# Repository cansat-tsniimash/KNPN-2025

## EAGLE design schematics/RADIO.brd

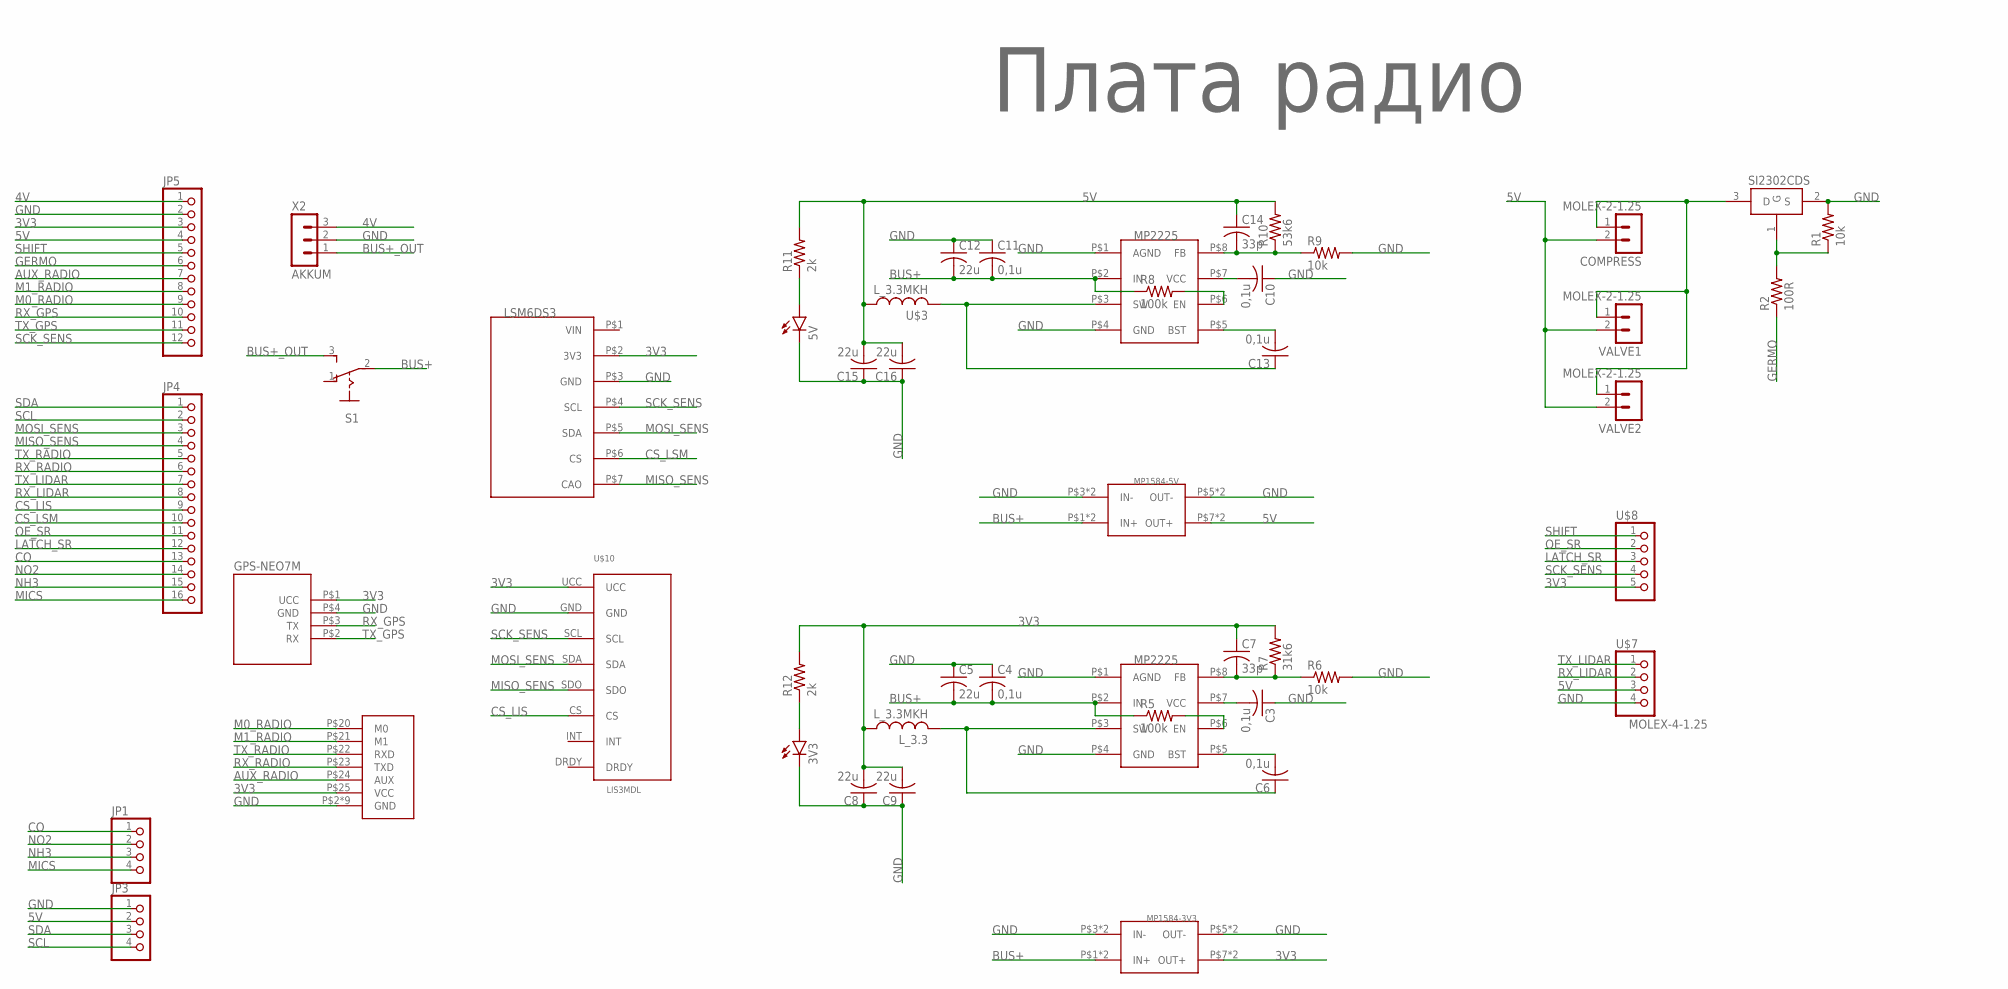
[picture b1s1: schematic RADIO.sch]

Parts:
3V3, 5V: LEDCHIP-LED0603; CHIP-LED0603
C3, C6, C10, C13: 0,1u; C0603
C4, C11: 0,1u; C1206
C5, C12: 22u; C0603
C7, C14: 33p; C0603
C8, C9, C15, C16: 22u; C1206
COMPRESS: MOLEX-2-1.25; 53047-02
GPS-NEO7M: GPS-NEO7M
JP1, JP3: PINHD-1X4; 1X04
JP4: PINHD-1X16; 1X16
JP5: PINHD-1X12; 1X12
LSM6DS3: LSM6DS3; LSM6DS3_WITHOUT
L_3.3: L_3.3MKH; L_SPM5020
MP1584-3V3: MP1584-B
MP1584-5V: MP1584; MP1584-B
R1, R6, R9: 10k; R0603
R2: 100R; R0603
R5, R8: 100k; R0603
R7: 31k6; R0603
R10: 53k6; R0603
R11, R12: 2k; R0603
RADIO: E220-400T22S
S1: UNICS-SWITCHSS_12D11; SS_12D11
SI2302CDS: SI2302CDS; SOT23-3
U$1: Плата радио; LOGO
U$2, U$5: MP2225; TSOT23-8
U$3: L_3.3MKH; L_SPM5020
U$7: MOLEX-4-1.25; 53047-04
U$8: MOLEX-5-1.25; 53047-05
U$10: LIS3MDL
VALVE1, VALVE2: MOLEX-2-1.25; 53047-02
X2: AKKUM; JST-3-2.5

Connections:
3V3: C7.1, C8.2, C9.2, GPS-NEO7M.P$1 (UCC), JP5.3, LSM6DS3.P$2 (3V3), L_3.3.P$1 (1), MP1584-3V3.P$7 (OUT+), MP1584-3V3.P$8 (OUT+), R7.2, R12.2, RADIO.P$25 (VCC), U$8.5, U$10.UCC
4V: JP5.1, X2.3
5V: C14.1, C15.2, C16.2, COMPRESS.2, JP3.2, JP5.4, MP1584-5V.P$7 (OUT+), MP1584-5V.P$8 (OUT+), R10.2, R11.2, U$3.P$1 (1), U$7.3, VALVE1.2, VALVE2.2
AUX_RADIO: JP5.7, RADIO.P$24 (AUX)
BUS+: C4.2, C5.2, C11.2, C12.2, MP1584-3V3.P$1 (IN+), MP1584-3V3.P$2 (IN+), MP1584-5V.P$1 (IN+), MP1584-5V.P$2 (IN+), R5.1, R8.1, S1.2, U$2.P$2 (IN), U$5.P$2 (IN)
BUS+_OUT: S1.3 (S), X2.1
CO: JP1.1, JP4.13
CS_LIS: JP4.9, U$10.CS
CS_LSM: JP4.10, LSM6DS3.P$6 (CS)
GERMO: JP5.6, R2.1
GND: 3V3.C, 5V.C, C3.1, C4.1, C5.1, C8.1, C9.1, C10.1, C11.1, C12.1, C15.1, C16.1, GPS-NEO7M.P$4 (GND), JP3.1, JP5.2, LSM6DS3.P$3 (GND), MP1584-3V3.P$3 (IN-), MP1584-3V3.P$4 (IN-), MP1584-3V3.P$5 (OUT-), MP1584-3V3.P$6 (OUT-), MP1584-5V.P$3 (IN-), MP1584-5V.P$4 (IN-), MP1584-5V.P$5 (OUT-), MP1584-5V.P$6 (OUT-), R1.2, R6.2, R9.2, RADIO.P$2 (GND), RADIO.P$8 (GND), RADIO.P$11 (GND), RADIO.P$13 (GND), RADIO.P$14 (GND), RADIO.P$15 (GND), RADIO.P$16 (GND), RADIO.P$19 (GND), RADIO.P$26 (GND), SI2302CDS.2 (S), U$2.P$1 (AGND), U$2.P$4 (GND), U$5.P$1 (AGND), U$5.P$4 (GND), U$7.4, U$10.GND, X2.2
LATCH_SR: JP4.12, U$8.3
M0_RADIO: JP5.9, RADIO.P$20 (M0)
M1_RADIO: JP5.8, RADIO.P$21 (M1)
MICS: JP1.4, JP4.16
MISO_SENS: JP4.4, LSM6DS3.P$7 (CAO), U$10.SDO
MOSI_SENS: JP4.3, LSM6DS3.P$5 (SDA), U$10.SDA
unnamed: R1.1, R2.2, SI2302CDS.1 (G)
unnamed: COMPRESS.1, SI2302CDS.3 (D), VALVE1.1, VALVE2.1
unnamed: C3.2, U$2.P$7 (VCC)
unnamed: R5.2, U$2.P$6 (EN)
unnamed: C6.2, U$2.P$5 (BST)
unnamed: C6.1, L_3.3.P$2 (2), U$2.P$3 (SW)
unnamed: C7.2, R6.1, R7.1, U$2.P$8 (FB)
unnamed: C10.2, U$5.P$7 (VCC)
unnamed: R8.2, U$5.P$6 (EN)
unnamed: C13.2, U$5.P$5 (BST)
unnamed: C13.1, U$3.P$2 (2), U$5.P$3 (SW)
unnamed: C14.2, R9.1, R10.1, U$5.P$8 (FB)
unnamed: 5V.A, R11.1
unnamed: 3V3.A, R12.1
NH3: JP1.3, JP4.15
NO2: JP1.2, JP4.14
OE_SR: JP4.11, U$8.2
RX_GPS: GPS-NEO7M.P$3 (TX), JP5.10
RX_LIDAR: JP4.8, U$7.2
RX_RADIO: JP4.6, RADIO.P$23 (TXD)
SCK_SENS: JP5.12, LSM6DS3.P$4 (SCL), U$8.4, U$10.SCL
SCL: JP3.4, JP4.2
SDA: JP3.3, JP4.1
SHIFT: JP5.5, U$8.1
TX_GPS: GPS-NEO7M.P$2 (RX), JP5.11
TX_LIDAR: JP4.7, U$7.1
TX_RADIO: JP4.5, RADIO.P$22 (RXD)

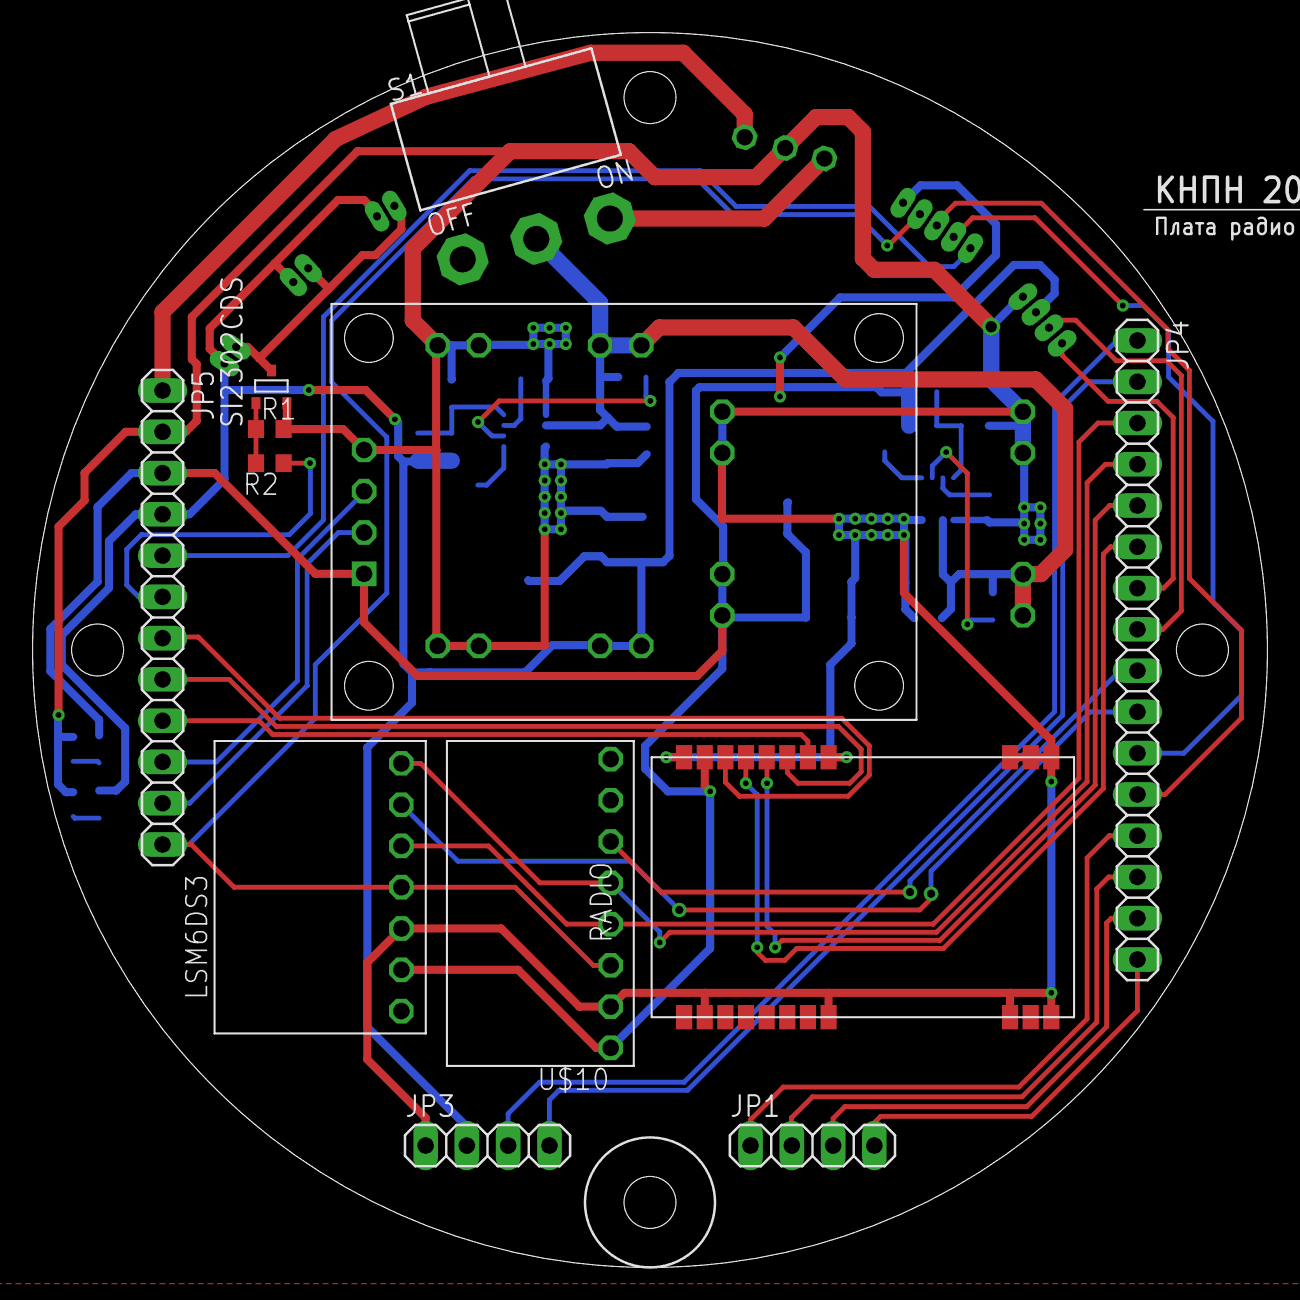
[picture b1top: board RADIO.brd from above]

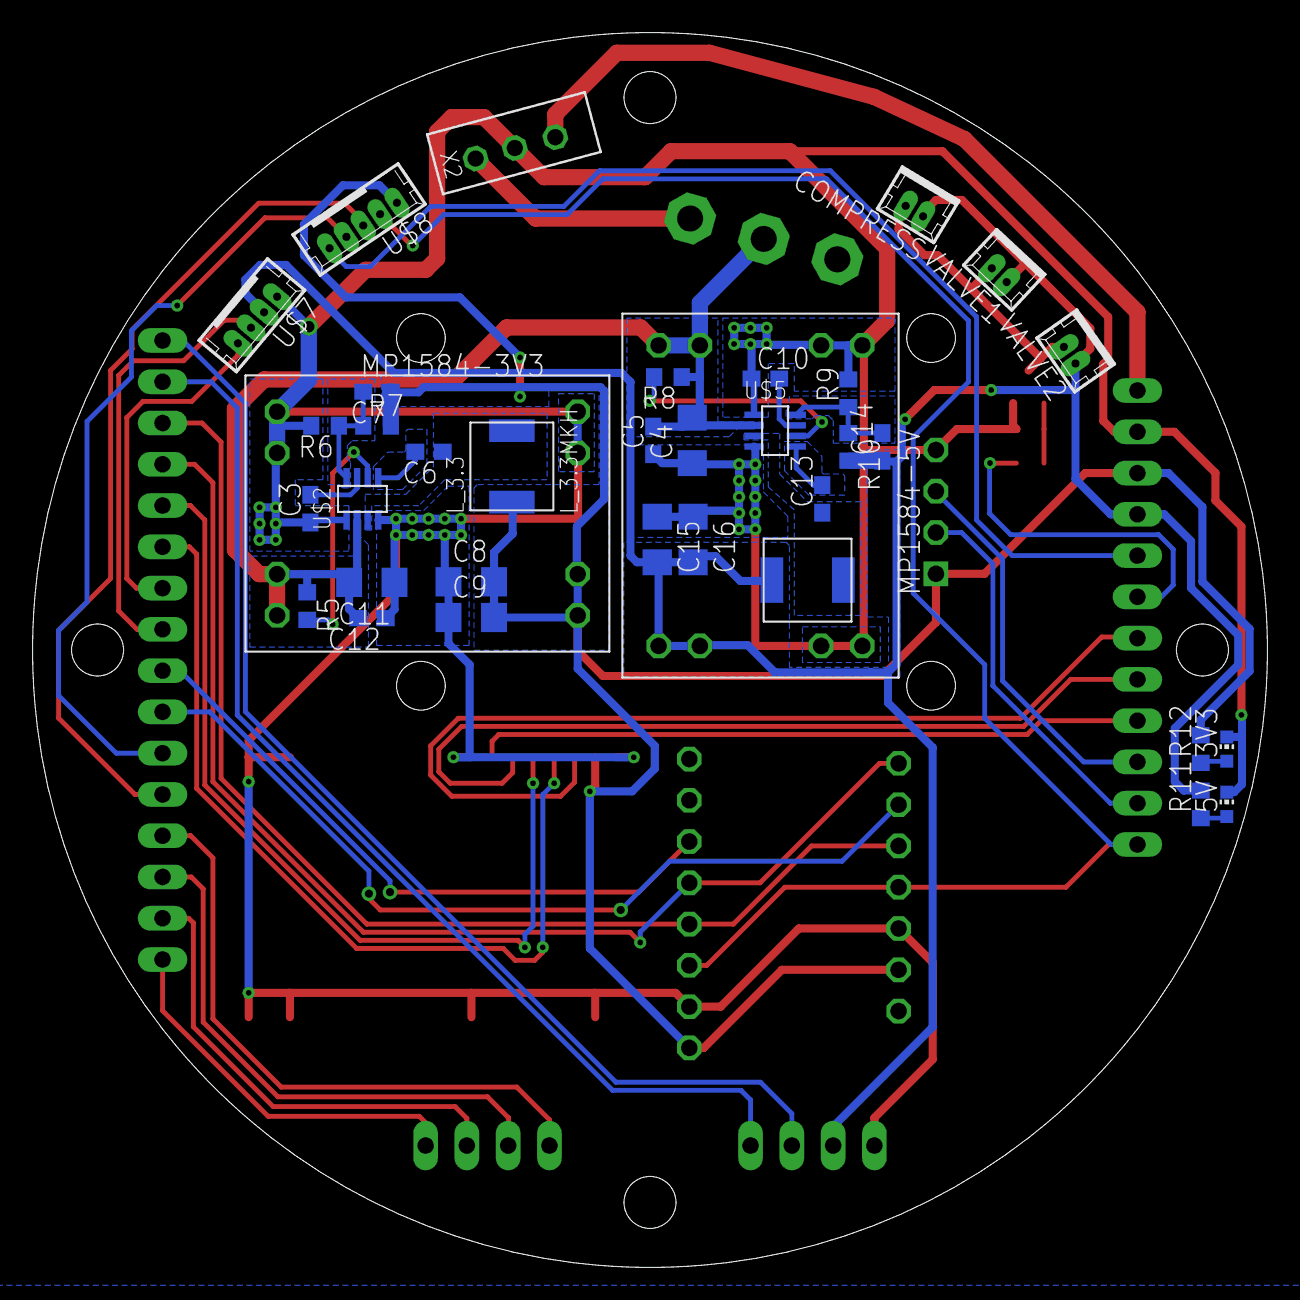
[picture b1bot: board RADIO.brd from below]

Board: 2 copper layers, 76.0 x 76.0 mm, 49 parts (36 on the bottom side), 44 nets.

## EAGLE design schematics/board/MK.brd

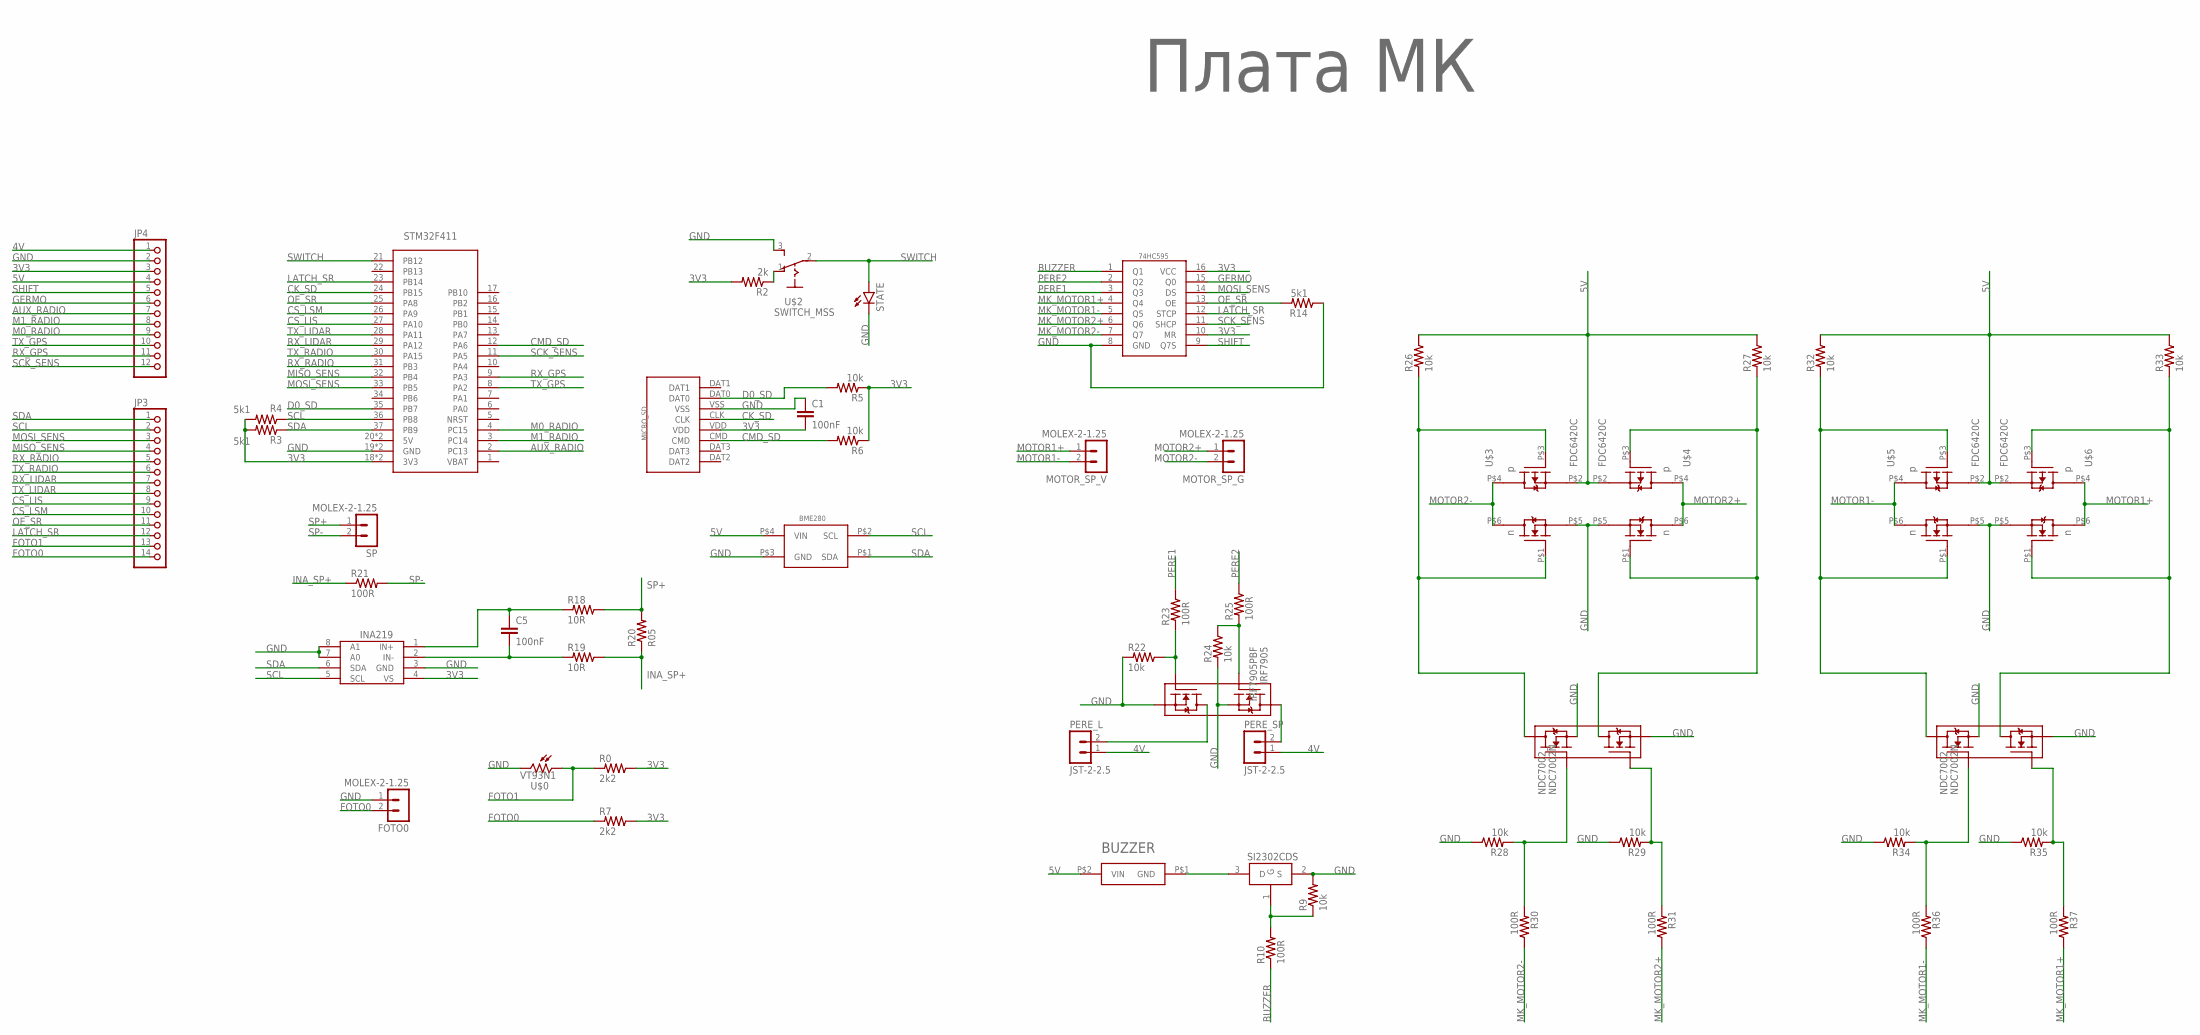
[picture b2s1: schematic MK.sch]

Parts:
74HC595: 74HC595; TSSOP16
BME280: BME280BME280-PINS-ONLY; BME280-PINS-ONLY
BUZZER: BUZZERS8R6; BUZZER-S8R12
C1, C5: 100nF; C0603
FOTO0: MOLEX-2-1.25; 53047-02
INA: INA219AID; SOT23-8
IRF7905: IRF7905PBF; SO8
JP3: PINHD-1X14; 1X14
JP4: PINHD-1X12; 1X12
MICRO_SD: SD
MOTOR_SP_G: MOLEX-2-1.25; 53047-02
MOTOR_SP_V: MOLEX-2-1.25; 53047-02
NDC7002, NDC7002_: NDC7002N; SOT23-6
PERE_L: JST-2-2.5
PERE_SP: JST-2-2.5
R0, R7: 2k2; R0603
R2: 2k; R0603
R3, R4, R14: 5k1; R0603
R5, R6, R9, R22, R24, R26, R27, R28, R29, R32, R33, R34, R35: 10k; R0603
R10, R23, R25, R30, R31, R36, R37: 100R; R0603
R18, R19: 10R; R0603
R20: R05; R2512
R21: 100R; 0207/15
SI2302: SI2302CDS; SOT23-3
SP: MOLEX-2-1.25; 53047-02
STATE: LEDCHIPLED_0603; CHIPLED_0603
STM32F411: STM32F411_BOARD
U$0: VT93N1
U$1: Плата МК; LOGO
U$2: SWITCH_MSS
U$3, U$4, U$5, U$6: FDC6420C; TSOP-6

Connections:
3V3: 74HC595.10 (MR), 74HC595.16 (VCC), C1.2, INA.4 (VS), JP4.3, MICRO_SD.VDD, R0.1, R2.2, R3.2, R4.2, R5.1, R6.1, R7.1, STM32F411.18 (3V3), STM32F411.40 (3V3)
4V: JP4.1, PERE_L.1, PERE_SP.1
5V: BME280.P$4 (VIN), BUZZER.P$2 (VIN), JP4.4, R26.1, R27.1, R32.1, R33.1, U$3.P$2 (PS), U$4.P$2 (PS), U$5.P$2 (PS), U$6.P$2 (PS)
AUX_RADIO: JP4.7, STM32F411.2 (PC13)
BUZZER: 74HC595.1 (Q1), R10.1
CK_SD: MICRO_SD.CLK, STM32F411.24 (PB15)
CMD_SD: MICRO_SD.CMD, R6.2, STM32F411.12 (PA6)
CS_LIS: JP3.9, STM32F411.27 (PA10)
CS_LSM: JP3.10, STM32F411.26 (PA9)
D0_SD: MICRO_SD.DAT0, R5.2, STM32F411.35 (PB7)
FOTO0: FOTO0.2, JP3.14, R7.2
FOTO1: JP3.13, R0.2, U$0.P$1 (1)
GERMO: 74HC595.15 (Q0), JP4.6
GND: 74HC595.8 (GND), BME280.P$3 (GND), C1.1, FOTO0.1, INA.3 (GND), INA.7 (A0), INA.8 (A1), IRF7905.1 (S2), IRF7905.3 (S1), JP4.2, MICRO_SD.VSS, NDC7002.2 (S2), NDC7002.5 (S1), NDC7002_.2 (S2), NDC7002_.5 (S1), R9.2, R14.1, R22.2, R24.2, R28.1, R29.1, R34.1, R35.1, SI2302.2 (S), STATE.C, STM32F411.19 (GND), STM32F411.39 (GND), U$0.P$2 (2), U$2.3 (S), U$3.P$5 (NS), U$4.P$5 (NS), U$5.P$5 (NS), U$6.P$5 (NS)
INA_SP+: R19.1, R20.1, R21.1
LATCH_SR: 74HC595.12 (STCP), JP3.12, STM32F411.23 (PB14)
M0_RADIO: JP4.9, STM32F411.4 (PC15)
M1_RADIO: JP4.8, STM32F411.3 (PC14)
MISO_SENS: JP3.4, STM32F411.32 (PB4)
MK_MOTOR1+: 74HC595.4 (Q4), R37.1
MK_MOTOR1-: 74HC595.5 (Q5), R36.1
MK_MOTOR2+: 74HC595.6 (Q6), R31.1
MK_MOTOR2-: 74HC595.7 (Q7), R30.1
MOSI_SENS: 74HC595.14 (DS), JP3.3, STM32F411.33 (PB5)
MOTOR1+: MOTOR_SP_V.1, U$6.P$4 (PD), U$6.P$6 (ND)
MOTOR1-: MOTOR_SP_V.2, U$5.P$4 (PD), U$5.P$6 (ND)
MOTOR2+: MOTOR_SP_G.1, U$4.P$4 (PD), U$4.P$6 (ND)
MOTOR2-: MOTOR_SP_G.2, U$3.P$4 (PD), U$3.P$6 (ND)
unnamed: R2.1, U$2.1 (O)
unnamed: BUZZER.P$1 (GND), SI2302.3 (D)
unnamed: R9.1, R10.2, SI2302.1 (G)
unnamed: C5.2, INA.2 (IN-), R19.2
unnamed: C5.1, INA.1 (IN+), R18.2
unnamed: IRF7905.7 (D2), IRF7905.8 (D2), PERE_L.2
unnamed: IRF7905.5 (D1), IRF7905.6 (D1), PERE_SP.2
unnamed: IRF7905.2 (G2), R22.1, R23.2
unnamed: IRF7905.4 (G1), R24.1, R25.2
unnamed: NDC7002.6 (D1), R32.2, U$5.P$1 (NG), U$5.P$3 (PG)
unnamed: NDC7002_.6 (D1), R26.2, U$3.P$1 (NG), U$3.P$3 (PG)
unnamed: NDC7002_.4 (D2), R27.2, U$4.P$1 (NG), U$4.P$3 (PG)
unnamed: NDC7002.4 (D2), R33.2, U$6.P$1 (NG), U$6.P$3 (PG)
unnamed: NDC7002.1 (G1), R34.2, R36.2
unnamed: NDC7002.3 (G2), R35.2, R37.2
unnamed: NDC7002_.1 (G1), R28.2, R30.2
unnamed: NDC7002_.3 (G2), R29.2, R31.2
OE_SR: 74HC595.13 (OE), JP3.11, R14.2, STM32F411.25 (PA8)
PERE1: 74HC595.3 (Q3), R23.1
PERE2: 74HC595.2 (Q2), R25.1
RX_GPS: JP4.11, STM32F411.9 (PA3)
RX_LIDAR: JP3.7, STM32F411.29 (PA12)
RX_RADIO: JP3.5, STM32F411.31 (PB3)
SCK_SENS: 74HC595.11 (SHCP), JP4.12, STM32F411.11 (PA5)
SCL: BME280.P$2 (SCL), INA.5 (SCL), JP3.2, R4.1, STM32F411.36 (PB8)
SDA: BME280.P$1 (SDA), INA.6 (SDA), JP3.1, R3.1, STM32F411.37 (PB9)
SHIFT: 74HC595.9 (Q7S), JP4.5
SP+: R18.1, R20.2, SP.1
SP-: R21.2, SP.2
SWITCH: STATE.A, STM32F411.21 (PB12), U$2.2
TX_GPS: JP4.10, STM32F411.8 (PA2)
TX_LIDAR: JP3.8, STM32F411.28 (PA11)
TX_RADIO: JP3.6, STM32F411.30 (PA15)

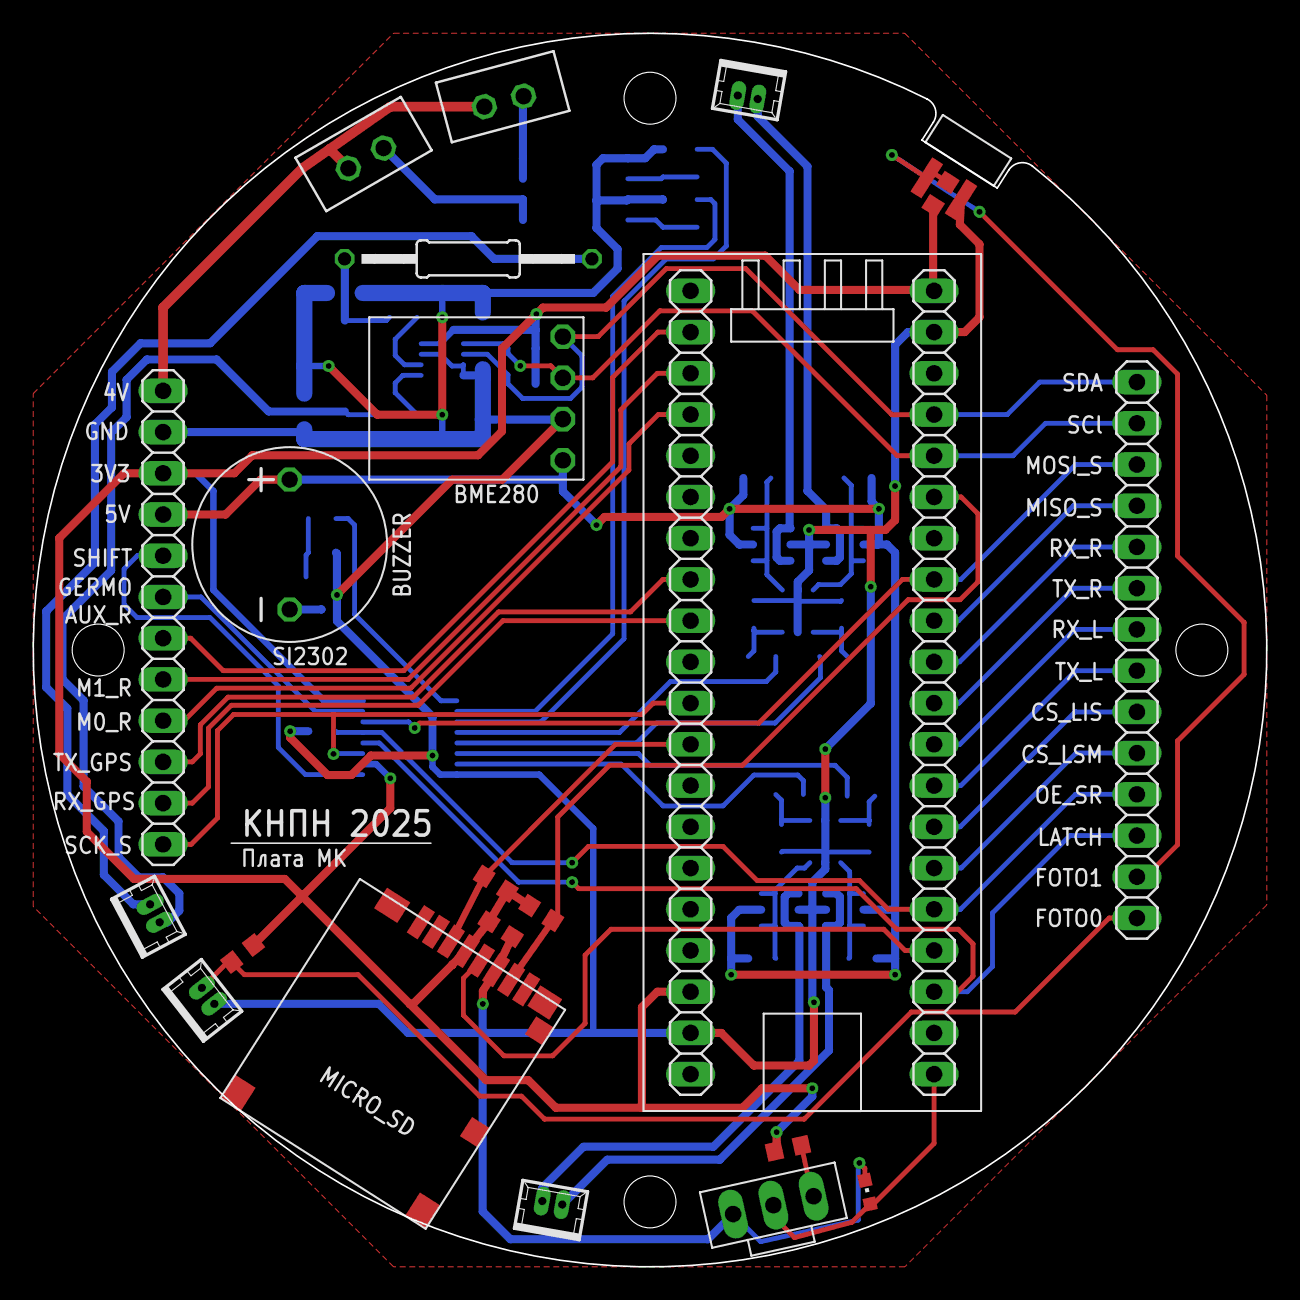
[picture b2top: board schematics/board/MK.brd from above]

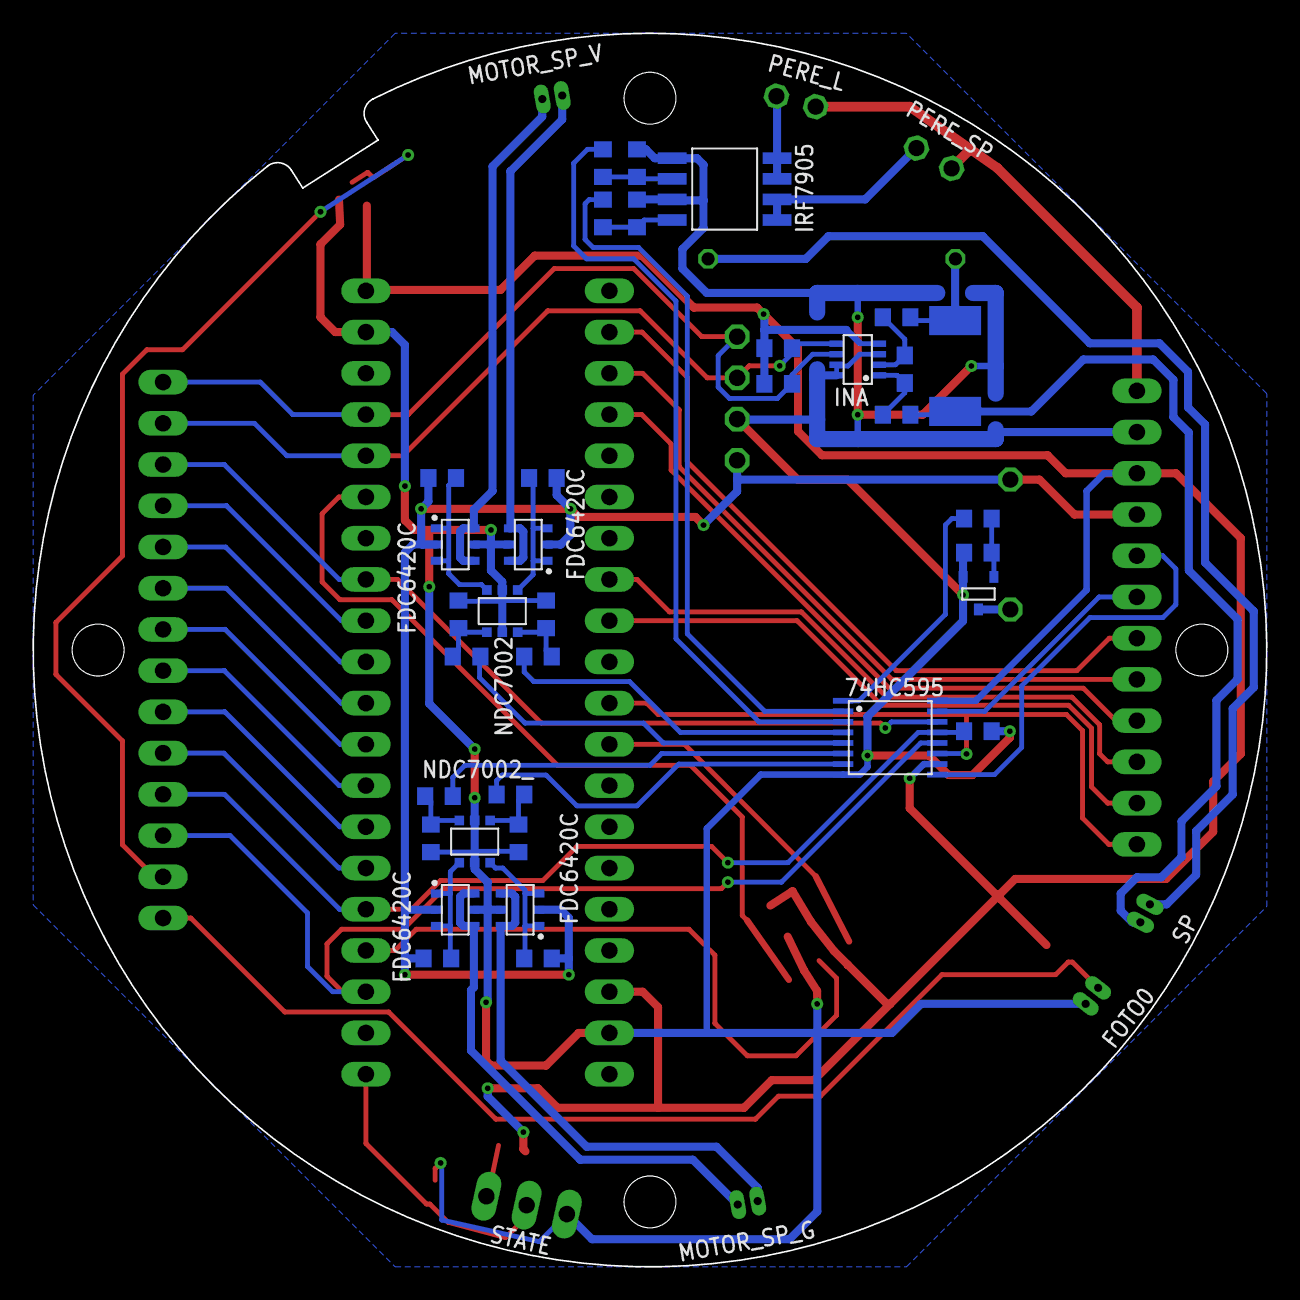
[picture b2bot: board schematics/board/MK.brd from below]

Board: 2 copper layers, 76.0 x 76.0 mm, 58 parts (35 on the bottom side), 61 nets.

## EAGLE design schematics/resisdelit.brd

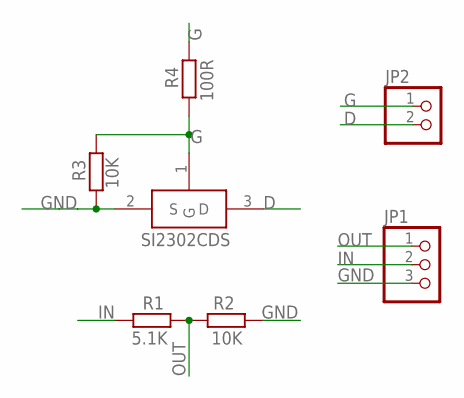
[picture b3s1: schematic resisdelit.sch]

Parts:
JP1: PINHD-1X3; 1X03
JP2: PINHD-1X2; 1X02
R1: 5.1K; R0603
R2, R3: 10K; R0603
R4: 100R; R0603
SI2300A: SI2302CDS; SOT23-3

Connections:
D: JP2.2, SI2300A.3 (D)
G: JP2.1, R3.2, R4.1, R4.2, SI2300A.1 (G)
GND: JP1.3, R2.2, R3.1, SI2300A.2 (S)
IN: JP1.2, R1.1
OUT: JP1.1, R1.2, R2.1

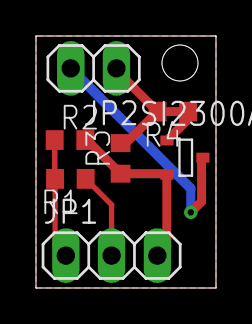
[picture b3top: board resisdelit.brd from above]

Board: 2 copper layers, 10.0 x 14.0 mm, 7 parts (0 on the bottom side), 5 nets.

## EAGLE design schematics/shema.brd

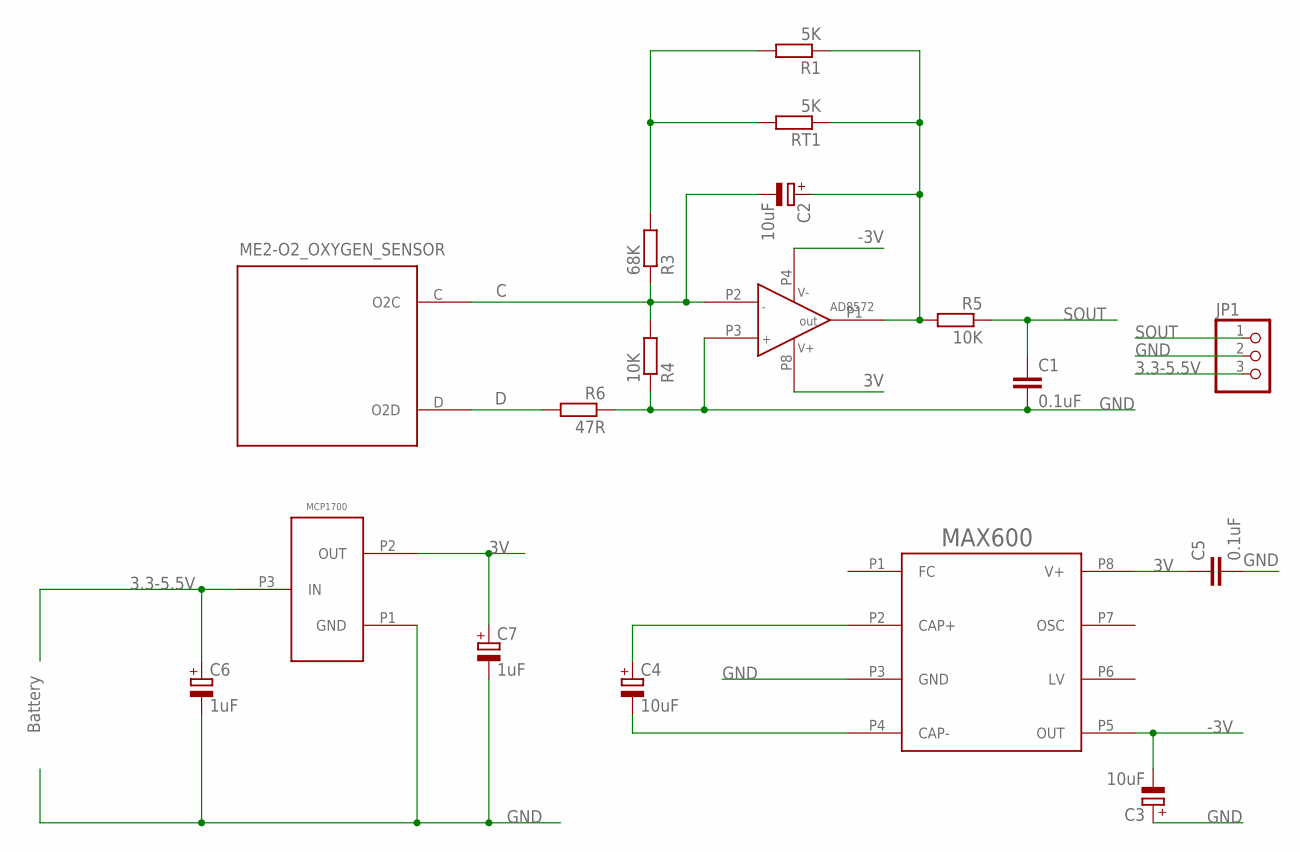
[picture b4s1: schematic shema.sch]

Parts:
AD8572: AD8572
C1, C5: 0.1uF; C0603
C2, C3, C4: 10uF; 153CLV-0405
C6, C7: 1uF; 153CLV-0405
JP1: PINHD-1X3; 1X03
MAX600: MAX660
MCP1700: MCP1700
ME2-O2_OXYGEN_SENSOR: ME2-O2_OXYGEN_SENSOR
R1: 5K; R0603
R3: 68K; R0603
R4, R5: 10K; R0603
R6: 47R; R0603
RT1: 5K; R0603

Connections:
3.3-5.5V: C6.+, JP1.3, MCP1700.P3 (IN)
3V: AD8572.P8 (V+), C5.1, C7.+, MAX600.P8 (V+), MCP1700.P2 (OUT)
-3V: AD8572.P4 (V-), C3.-, MAX600.P5 (OUT)
C: AD8572.P2 (-IN), C2.-, ME2-O2_OXYGEN_SENSOR.C (O2C), R3.1, R4.2
D: ME2-O2_OXYGEN_SENSOR.D (O2D), R6.2
GND: AD8572.P3 (+IN), C1.2, C3.+, C5.2, C6.-, C7.-, JP1.2, MAX600.P3 (GND), MCP1700.P1 (GND), R4.1, R6.1
unnamed: AD8572.P1 (OUT), C2.+, R1.1, R5.2, RT1.1
unnamed: R1.2, R3.2, RT1.2
unnamed: C4.+, MAX600.P2 (CAP+)
unnamed: C4.-, MAX600.P4 (CAP-)
SOUT: C1.1, JP1.1, R5.1

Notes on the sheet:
Battery

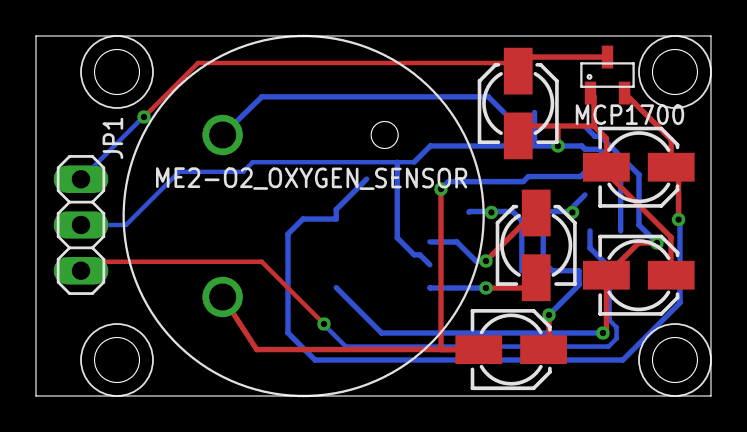
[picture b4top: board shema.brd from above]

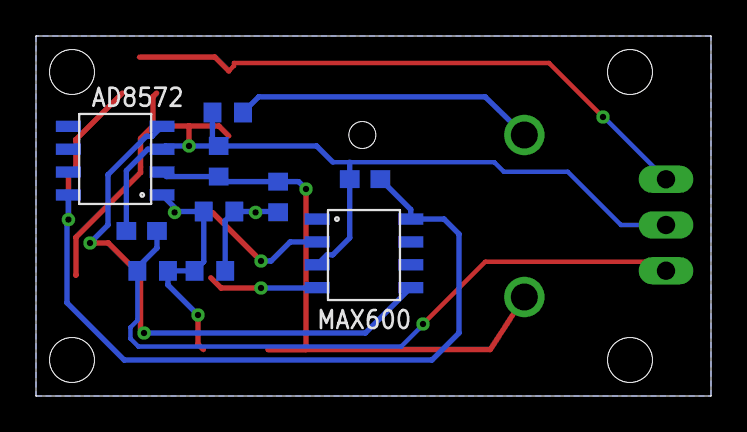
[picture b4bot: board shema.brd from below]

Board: 2 copper layers, 37.5 x 20.0 mm, 18 parts (10 on the bottom side), 11 nets.

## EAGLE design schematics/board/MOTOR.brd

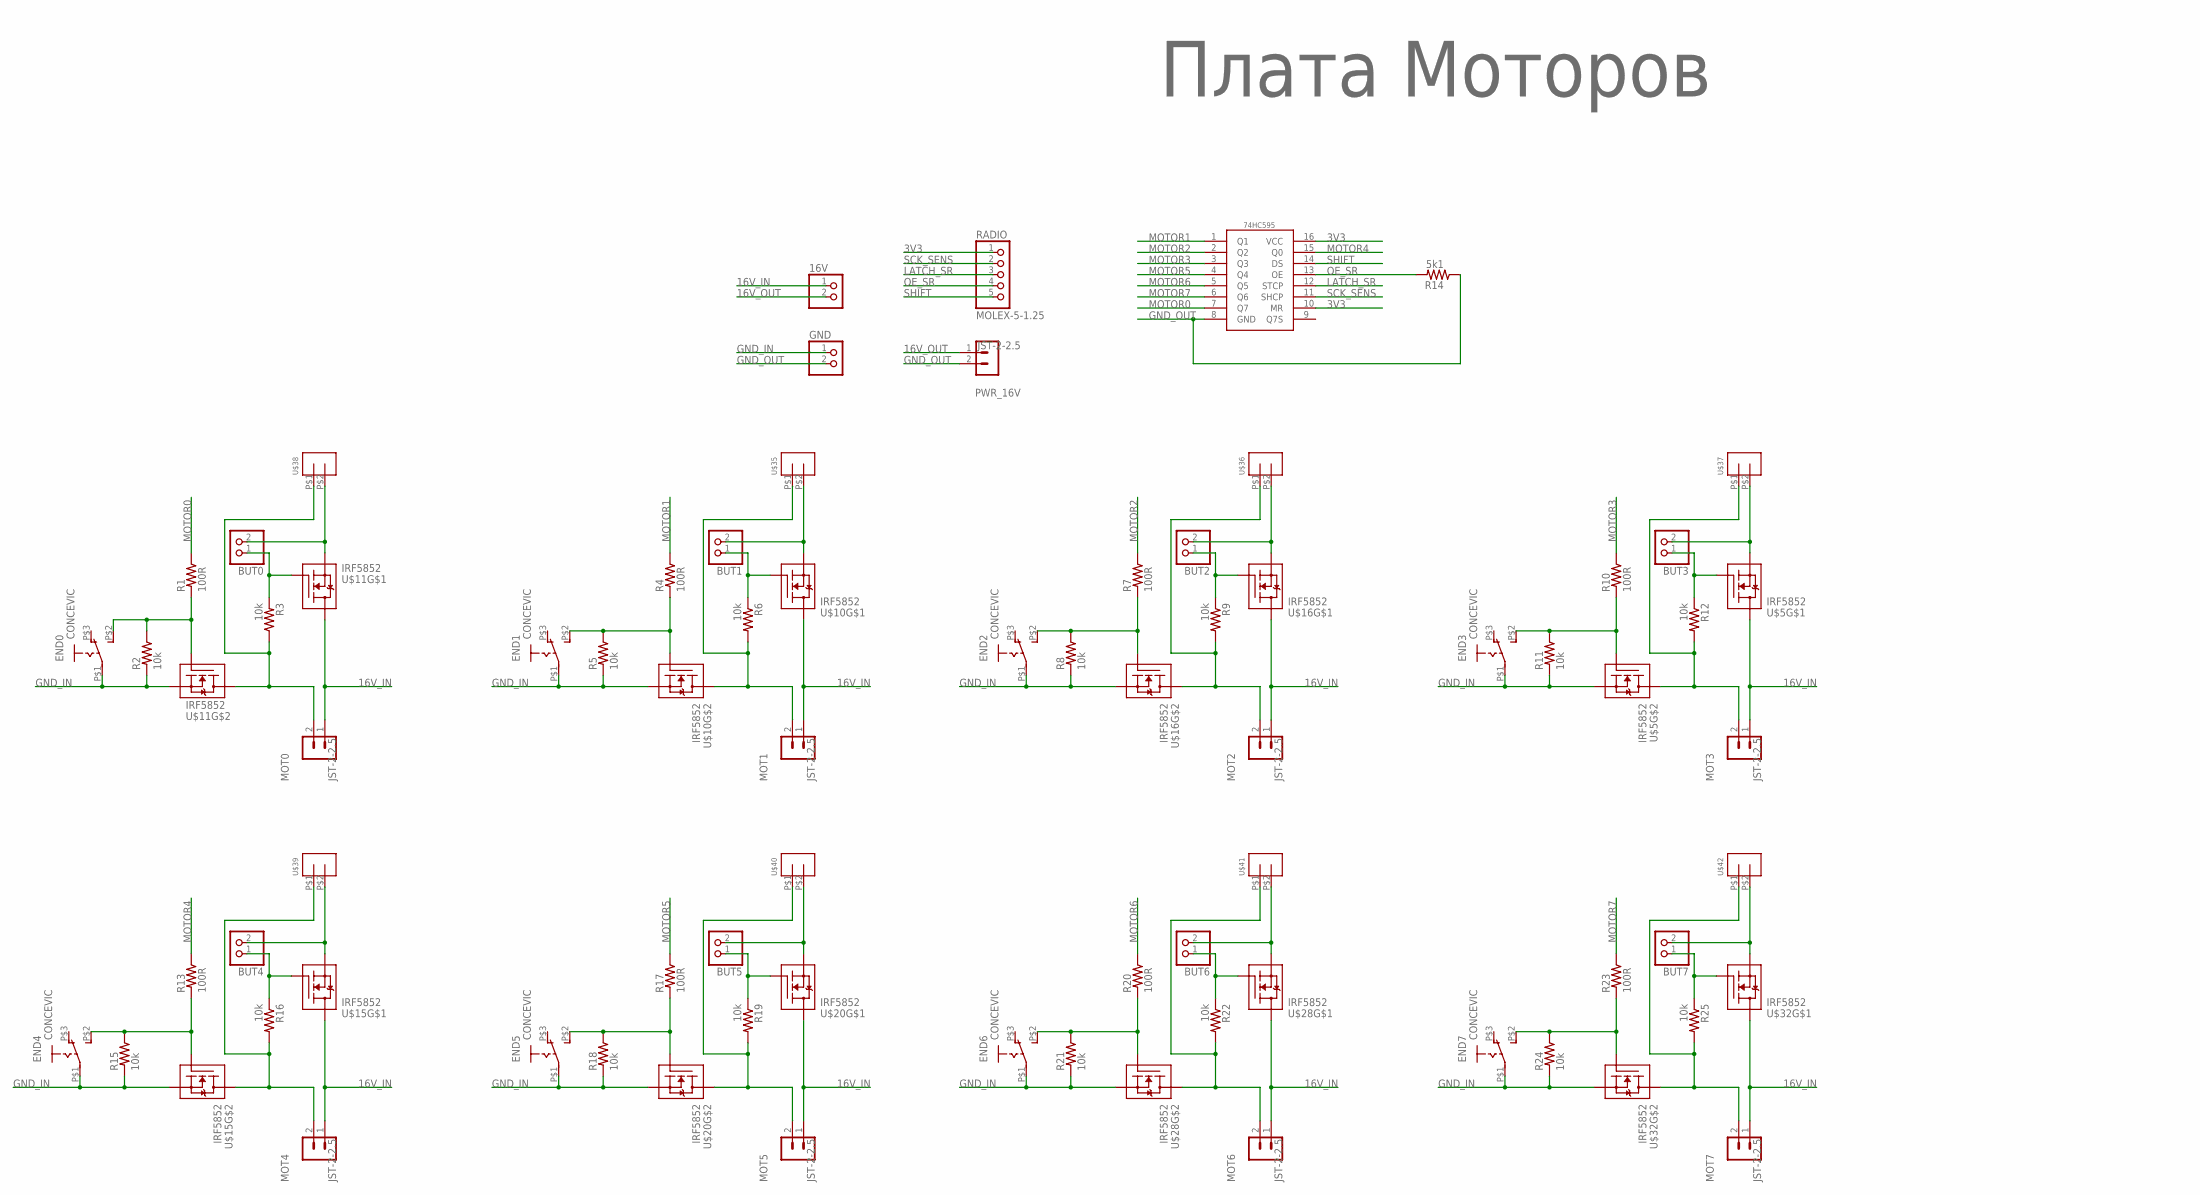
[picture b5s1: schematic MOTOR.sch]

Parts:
16V: PINHD-1X2/90; 1X02/90
74HC595: 74HC595; TSSOP16
BUT0, BUT1, BUT2, BUT3, BUT4, BUT5, BUT6, BUT7: PINHD-1X2; 1X02
END0, END1, END2, END3, END4, END5, END6, END7: CONCEVIC
GND: PINHD-1X2/90; 1X02/90
MOT0, MOT1, MOT2, MOT3, MOT4, MOT5, MOT6, MOT7: JST-2-2.5
PWR_16V: JST-2-2.5
R1, R4, R7, R10, R13, R17, R20, R23: 100R; R0603
R2, R3, R5, R6, R8, R9, R11, R12, R15, R16, R18, R19, R21, R22, R24, R25: 10k; R0603
R14: 5k1; R0603
RADIO: MOLEX-5-1.25; 53047-05
U$5, U$10, U$11, U$15, U$16, U$20, U$28, U$32: IRF5852; TSOP-6
U$9: Плата Моторов; LOGO
U$35, U$36, U$37, U$38, U$39, U$40, U$41, U$42: CONTACT_SIDE_4MM_2PIN

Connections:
3V3: 74HC595.10 (MR), 74HC595.16 (VCC), RADIO.1
16V_IN: 16V.1, MOT0.1, MOT1.1, MOT2.1, MOT3.1, MOT4.1, MOT5.1, MOT6.1, MOT7.1, U$5.P$6 (D1), U$10.P$6 (D1), U$11.P$6 (D1), U$15.P$6 (D1), U$16.P$6 (D1), U$20.P$6 (D1), U$28.P$6 (D1), U$32.P$6 (D1)
16V_OUT: 16V.2, PWR_16V.1
GND_IN: END0.P$1, END1.P$1, END2.P$1, END3.P$1, END4.P$1, END5.P$1, END6.P$1, END7.P$1, GND.1, R2.2, R5.2, R8.2, R11.2, R15.2, R18.2, R21.2, R24.2, U$5.P$2 (S1), U$10.P$2 (S1), U$11.P$2 (S1), U$15.P$2 (S1), U$16.P$2 (S1), U$20.P$2 (S1), U$28.P$2 (S1), U$32.P$2 (S1)
GND_OUT: 74HC595.8 (GND), GND.2, PWR_16V.2, R14.1
LATCH_SR: 74HC595.12 (STCP), RADIO.3
MOTOR0: 74HC595.7 (Q7), R1.1
MOTOR1: 74HC595.1 (Q1), R4.1
MOTOR2: 74HC595.2 (Q2), R7.1
MOTOR3: 74HC595.3 (Q3), R10.1
MOTOR4: 74HC595.15 (Q0), R13.1
MOTOR5: 74HC595.4 (Q4), R17.1
MOTOR6: 74HC595.5 (Q5), R20.1
MOTOR7: 74HC595.6 (Q6), R23.1
unnamed: MOT0.2, R3.1, U$11.P$4 (D1), U$38.P$1
unnamed: MOT1.2, R6.2, U$10.P$4 (D1), U$35.P$1
unnamed: END1.P$2 (S), R4.2, R5.1, U$10.P$3 (G1)
unnamed: END0.P$2 (S), R1.2, R2.1, U$11.P$3 (G1)
unnamed: BUT1.2, U$10.P$5 (S1), U$35.P$2
unnamed: BUT0.1, R3.2, U$11.P$1 (G1)
unnamed: BUT1.1, R6.1, U$10.P$1 (G1)
unnamed: BUT0.2, U$11.P$5 (S1), U$38.P$2
unnamed: MOT2.2, R9.2, U$16.P$4 (D1), U$36.P$1
unnamed: BUT2.2, U$16.P$5 (S1), U$36.P$2
unnamed: END3.P$2 (S), R10.2, R11.1, U$5.P$3 (G1)
unnamed: END2.P$2 (S), R7.2, R8.1, U$16.P$3 (G1)
unnamed: BUT2.1, R9.1, U$16.P$1 (G1)
unnamed: MOT3.2, R12.2, U$5.P$4 (D1), U$37.P$1
unnamed: BUT3.2, U$5.P$5 (S1), U$37.P$2
unnamed: BUT3.1, R12.1, U$5.P$1 (G1)
unnamed: END4.P$2 (S), R13.2, R15.1, U$15.P$3 (G1)
unnamed: MOT4.2, R16.2, U$15.P$4 (D1), U$39.P$1
unnamed: BUT4.2, U$15.P$5 (S1), U$39.P$2
unnamed: BUT4.1, R16.1, U$15.P$1 (G1)
unnamed: END5.P$2 (S), R17.2, R18.1, U$20.P$3 (G1)
unnamed: MOT5.2, R19.2, U$20.P$4 (D1), U$40.P$1
unnamed: BUT5.2, U$20.P$5 (S1), U$40.P$2
unnamed: BUT5.1, R19.1, U$20.P$1 (G1)
unnamed: END6.P$2 (S), R20.2, R21.1, U$28.P$3 (G1)
unnamed: MOT6.2, R22.2, U$28.P$4 (D1), U$41.P$1
unnamed: BUT6.2, U$28.P$5 (S1), U$41.P$2
unnamed: BUT6.1, R22.1, U$28.P$1 (G1)
unnamed: END7.P$2 (S), R23.2, R24.1, U$32.P$3 (G1)
unnamed: MOT7.2, R25.2, U$32.P$4 (D1), U$42.P$1
unnamed: BUT7.2, U$32.P$5 (S1), U$42.P$2
unnamed: BUT7.1, R25.1, U$32.P$1 (G1)
OE_SR: 74HC595.13 (OE), R14.2, RADIO.4
SCK_SENS: 74HC595.11 (SHCP), RADIO.2
SHIFT: 74HC595.14 (DS), RADIO.5
